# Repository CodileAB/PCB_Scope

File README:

Wolley Scope
------------

Wolley Scope is a CAN bus analyzer made primarily for the Wolley ecosystem.

It communicates with the PC over UART using an FT232XS.

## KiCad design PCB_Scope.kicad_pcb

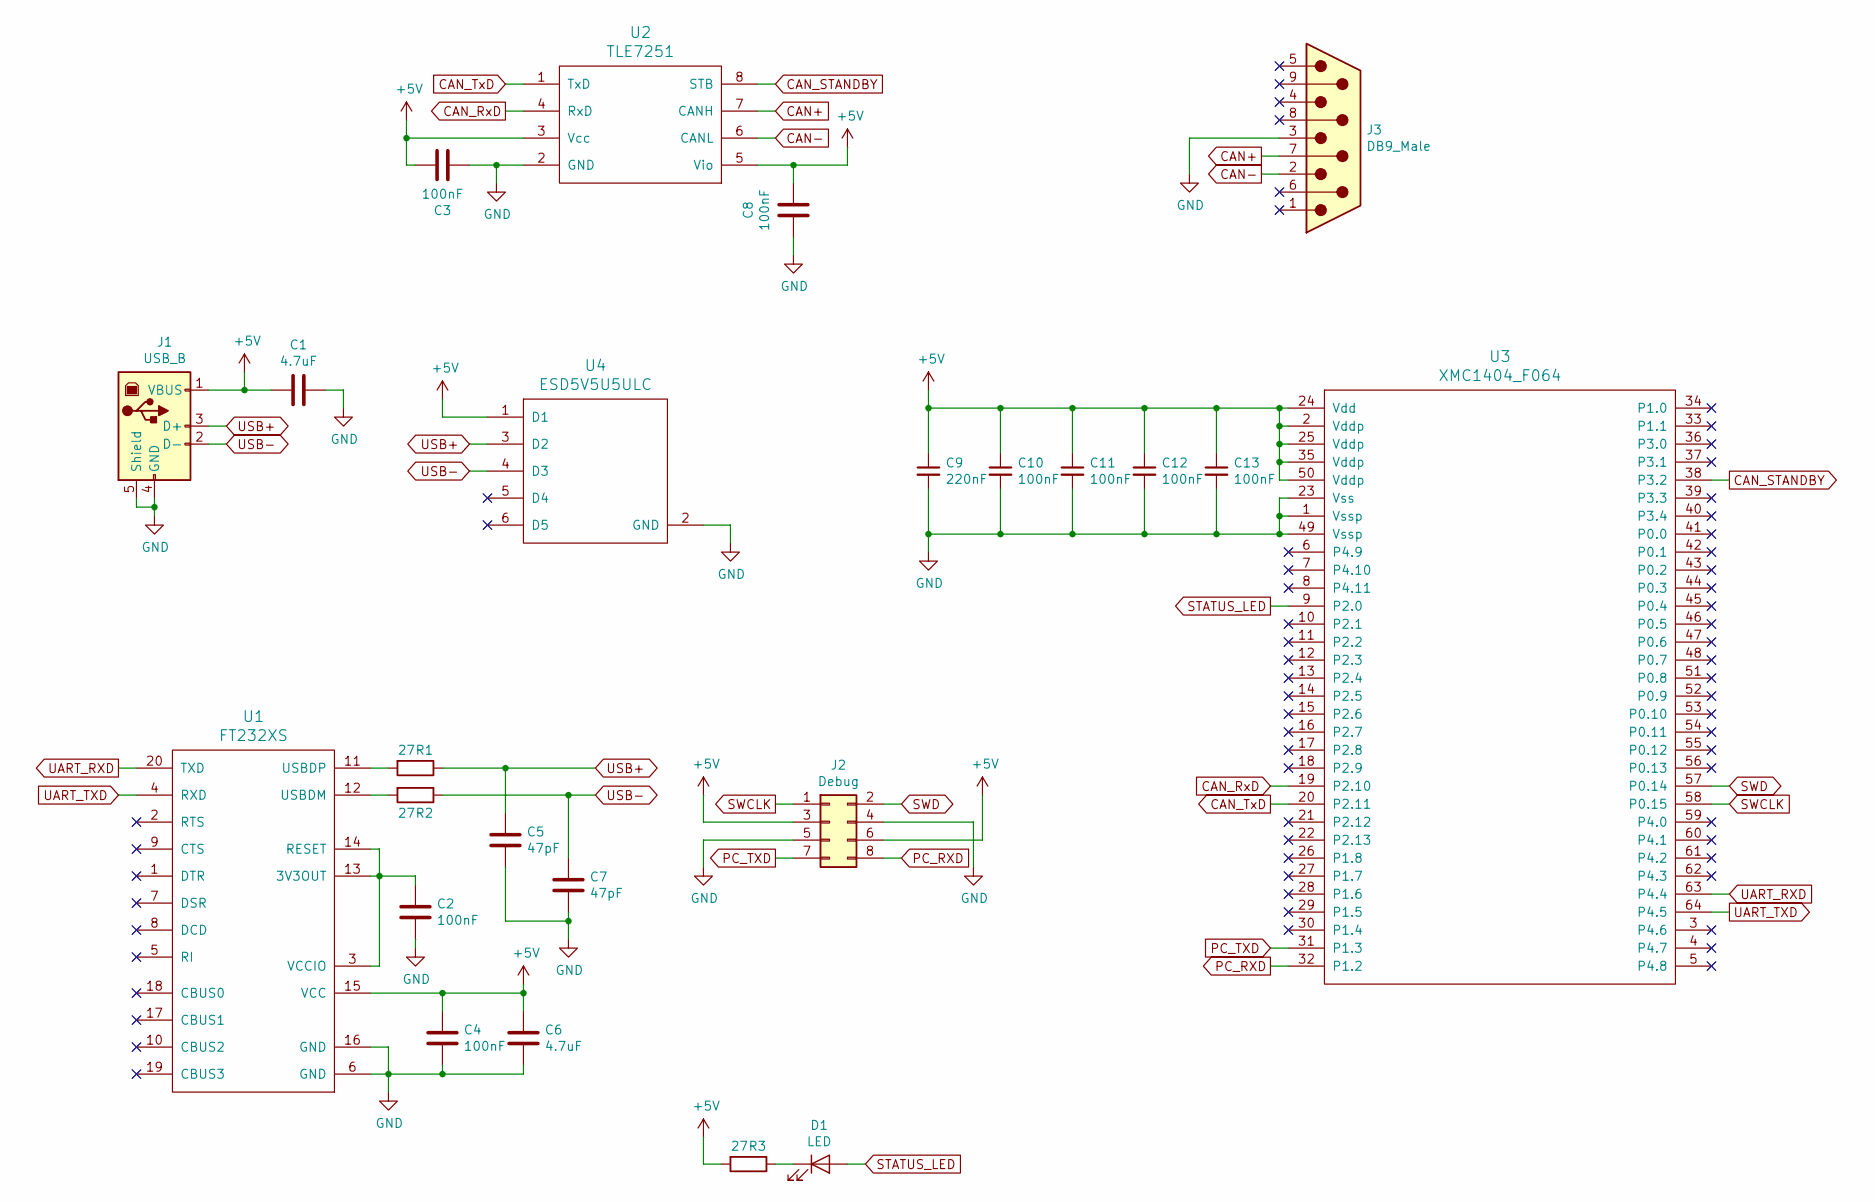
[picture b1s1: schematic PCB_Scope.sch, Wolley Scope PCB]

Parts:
C1, C6: 4.7uF; C_0805_HandSoldering
C2, C3, C4, C8, C10, C11, C12, C13: 100nF; C_0805_HandSoldering
C5, C7: 47pF; C_0805_HandSoldering
C9: 220nF; C_0805_HandSoldering
D1: LED; D_0805
J1: USB_B; Conn_USB-B_TE_292304-1_THT
J2: Debug; Pin_Header_Straight_2x04_Pitch2.54mm_SMD
J3: DB9_Male; Conn_D-Sub9_Harting_09651626813_THT
R1, R2, R3: 27; R_0805_HandSoldering
U1: FT232XS; QSOP-20_3.9x8.7mm_Pitch0.635mm
U2: TLE7251; SOIC-8_3.9x4.9mm_Pitch1.27mm
U3: XMC1404_F064; TQFP-64_10x10mm_Pitch0.5mm_Handsoldering
U4: ESD5V5U5ULC; TSOP-6_1.65x3.05mm_Pitch0.95mm

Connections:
+5V: C1.2, C3.1, C4.1, C6.1, C8.1, C9.1, C10.1, C11.1, C12.1, C13.1, J1.1 (VBUS), J2.3, J2.6, R3.2, U1.15 (VCC), U2.3 (Vcc), U2.5 (Vio), U3.2 (Vddp), U3.24 (Vdd), U3.25 (Vddp), U3.35 (Vddp), U3.50 (Vddp), U4.1 (D1)
CAN+: J3.7, U2.7 (CANH)
CAN-: J3.2, U2.6 (CANL)
CAN_RxD: U2.4 (RxD), U3.19 (P2.10)
CAN_STANDBY: U2.8 (STB), U3.38 (P3.2)
CAN_TxD: U2.1 (TxD), U3.20 (P2.11)
GND: C1.1, C2.2, C3.2, C4.2, C5.2, C6.2, C7.2, C8.2, C9.2, C10.2, C11.2, C12.2, C13.2, J1.4 (GND), J1.5 (Shield), J2.4, J2.5, J3.3, U1.6 (GND), U1.16 (GND), U2.2 (GND), U3.1 (Vssp), U3.23 (Vss), U3.49 (Vssp), U4.2 (GND)
unnamed: C2.1, U1.3 (VCCIO), U1.13 (3V3OUT), U1.14 (RESET)
unnamed: D1.1 (K), R3.1
unnamed: R1.2, U1.11 (USBDP)
unnamed: R2.2, U1.12 (USBDM)
PC_RXD: J2.8, U3.32 (P1.2)
PC_TXD: J2.7, U3.31 (P1.3)
STATUS_LED: D1.2 (A), U3.9 (P2.0)
SWCLK: J2.1, U3.58 (P0.15)
SWD: J2.2, U3.57 (P0.14)
UART_RXD: U1.20 (TXD), U3.63 (P4.4)
UART_TXD: U1.4 (RXD), U3.64 (P4.5)
USB+: C5.1, J1.3 (D+), R1.1, U4.3 (D2)
USB-: C7.1, J1.2 (D-), R2.1, U4.4 (D3)

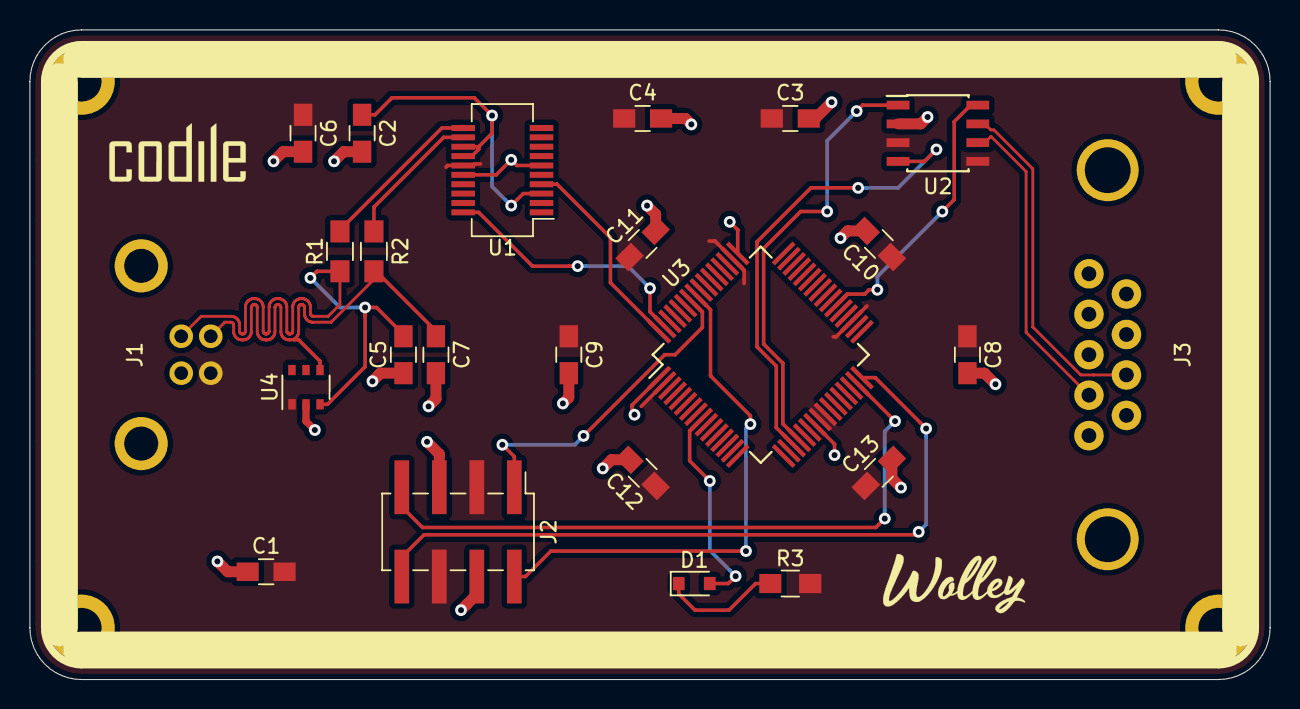
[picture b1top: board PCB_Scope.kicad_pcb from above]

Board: 2 copper layers, 84.0 x 44.0 mm, 24 parts (0 on the bottom side), 20 nets.

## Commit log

2019-06-16 Add KiCad project files
2020-12-07 Add logotype
2020-12-07 Add README file
